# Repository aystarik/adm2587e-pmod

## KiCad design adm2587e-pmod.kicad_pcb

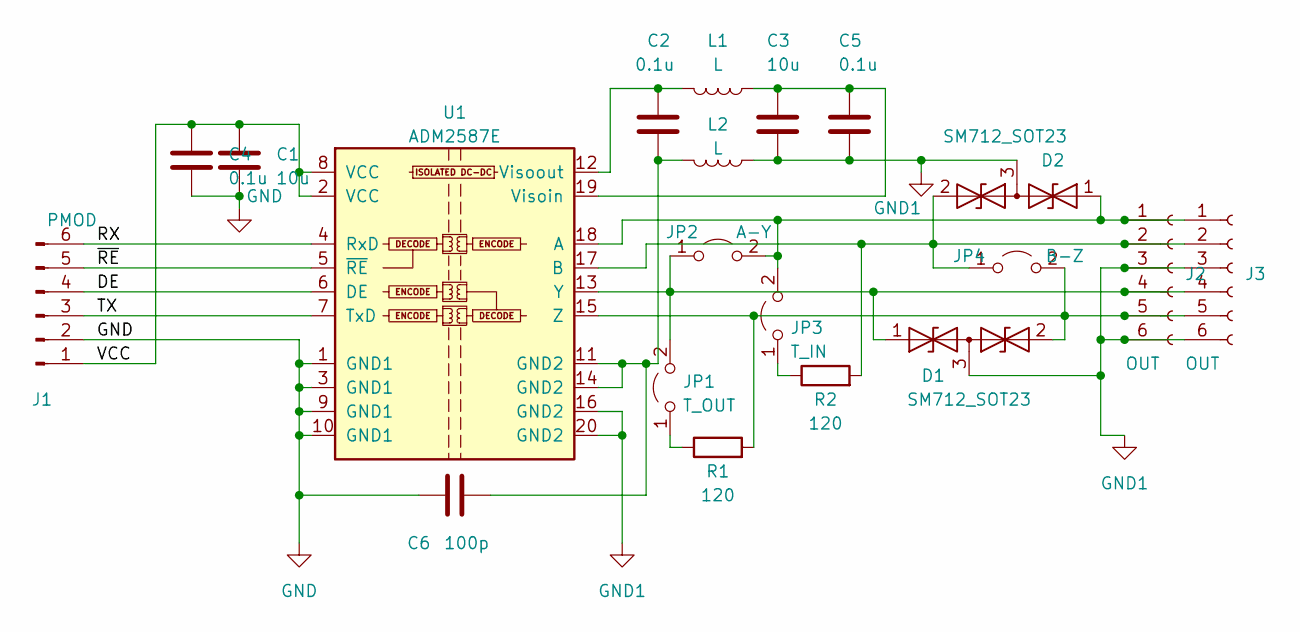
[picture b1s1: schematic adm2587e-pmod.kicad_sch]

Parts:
C1, C3: 10u; C_0603_1608Metric_Pad1.08x0.95mm_HandSolder
C2, C4, C5: 0.1u; C_0603_1608Metric_Pad1.08x0.95mm_HandSolder
C6: 100p; C_1812_4532Metric_Pad1.57x3.40mm_HandSolder
D1, D2: SM712_SOT23; SOT-23
J1: PMOD; PinHeader_1x06_P2.54mm_Horizontal
J2, J3: OUT; PinHeader_1x06_P2.54mm_Vertical
JP1: T_OUT; PinHeader_1x02_P2.54mm_Vertical
JP2: A-Y; PinHeader_1x02_P2.54mm_Vertical
JP3: T_IN; PinHeader_1x02_P2.54mm_Vertical
JP4: B-Z; PinHeader_1x02_P2.54mm_Vertical
L1, L2: L; L_0603_1608Metric_Pad1.05x0.95mm_HandSolder
R1, R2: 120; R_0603_1608Metric_Pad0.98x0.95mm_HandSolder
U1: ADM2587E; SOIC-20W_7.5x12.8mm_P1.27mm

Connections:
/DE: J1.4, U1.6 (DE)
/RX: J1.6, U1.4 (RxD)
/TX: J1.3, U1.7 (TxD)
/VCC: C1.2, C4.1, J1.1, U1.2 (VCC), U1.8 (VCC)
/~RE: J1.5, U1.5 (~RE)
GND: C1.1, C4.2, C6.1, J1.2, U1.1 (GND1), U1.3 (GND1), U1.9 (GND1), U1.10 (GND1)
GND1: C3.2, C5.2, D1.3 (common), D2.3 (common), J2.3, J2.6, J3.3, J3.6, L2.1, U1.16 (GND2), U1.20 (GND2)
unnamed: D1.1 (A1), J2.4, J3.4, JP1.2 (B), JP2.1 (A), U1.13 (Y)
unnamed: D1.2 (A2), J2.5, J3.5, JP4.2 (B), R1.2, U1.15 (Z)
unnamed: D2.1 (A1), J2.1, J3.1, JP2.2 (B), JP3.2 (B), U1.18 (A)
unnamed: D2.2 (A2), J2.2, J3.2, JP4.1 (A), R2.2, U1.17 (B)
unnamed: JP1.1 (A), R1.1
unnamed: JP3.1 (A), R2.1
unnamed: C2.2, C6.2, L2.2, U1.11 (GND2), U1.14 (GND2)
unnamed: C3.1, C5.1, L1.1, U1.19 (Visoin)
unnamed: C2.1, L1.2, U1.12 (Visoout)

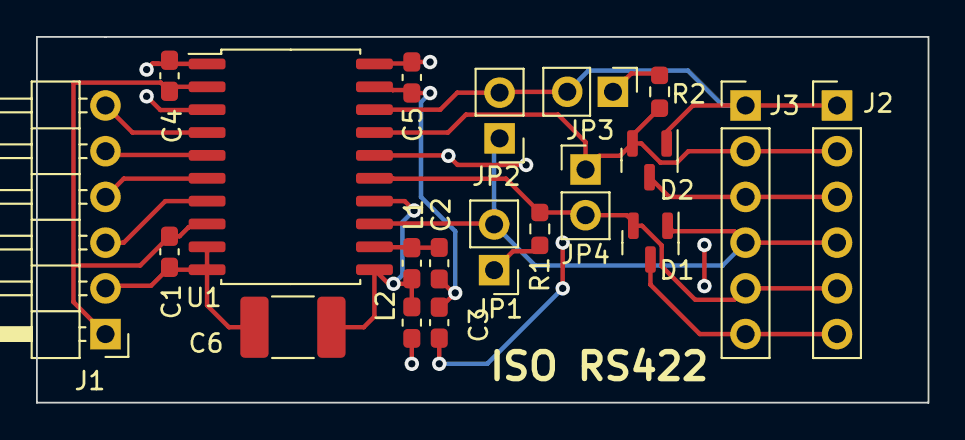
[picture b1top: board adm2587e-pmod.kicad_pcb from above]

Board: 2 copper layers, 49.5 x 20.3 mm, 20 parts (0 on the bottom side), 16 nets.

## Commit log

2022-01-05 first
2022-01-05 PMOD doc
2022-01-06 rename
2022-01-06 clear the GND1 plane under filter
2022-01-06 more polish
